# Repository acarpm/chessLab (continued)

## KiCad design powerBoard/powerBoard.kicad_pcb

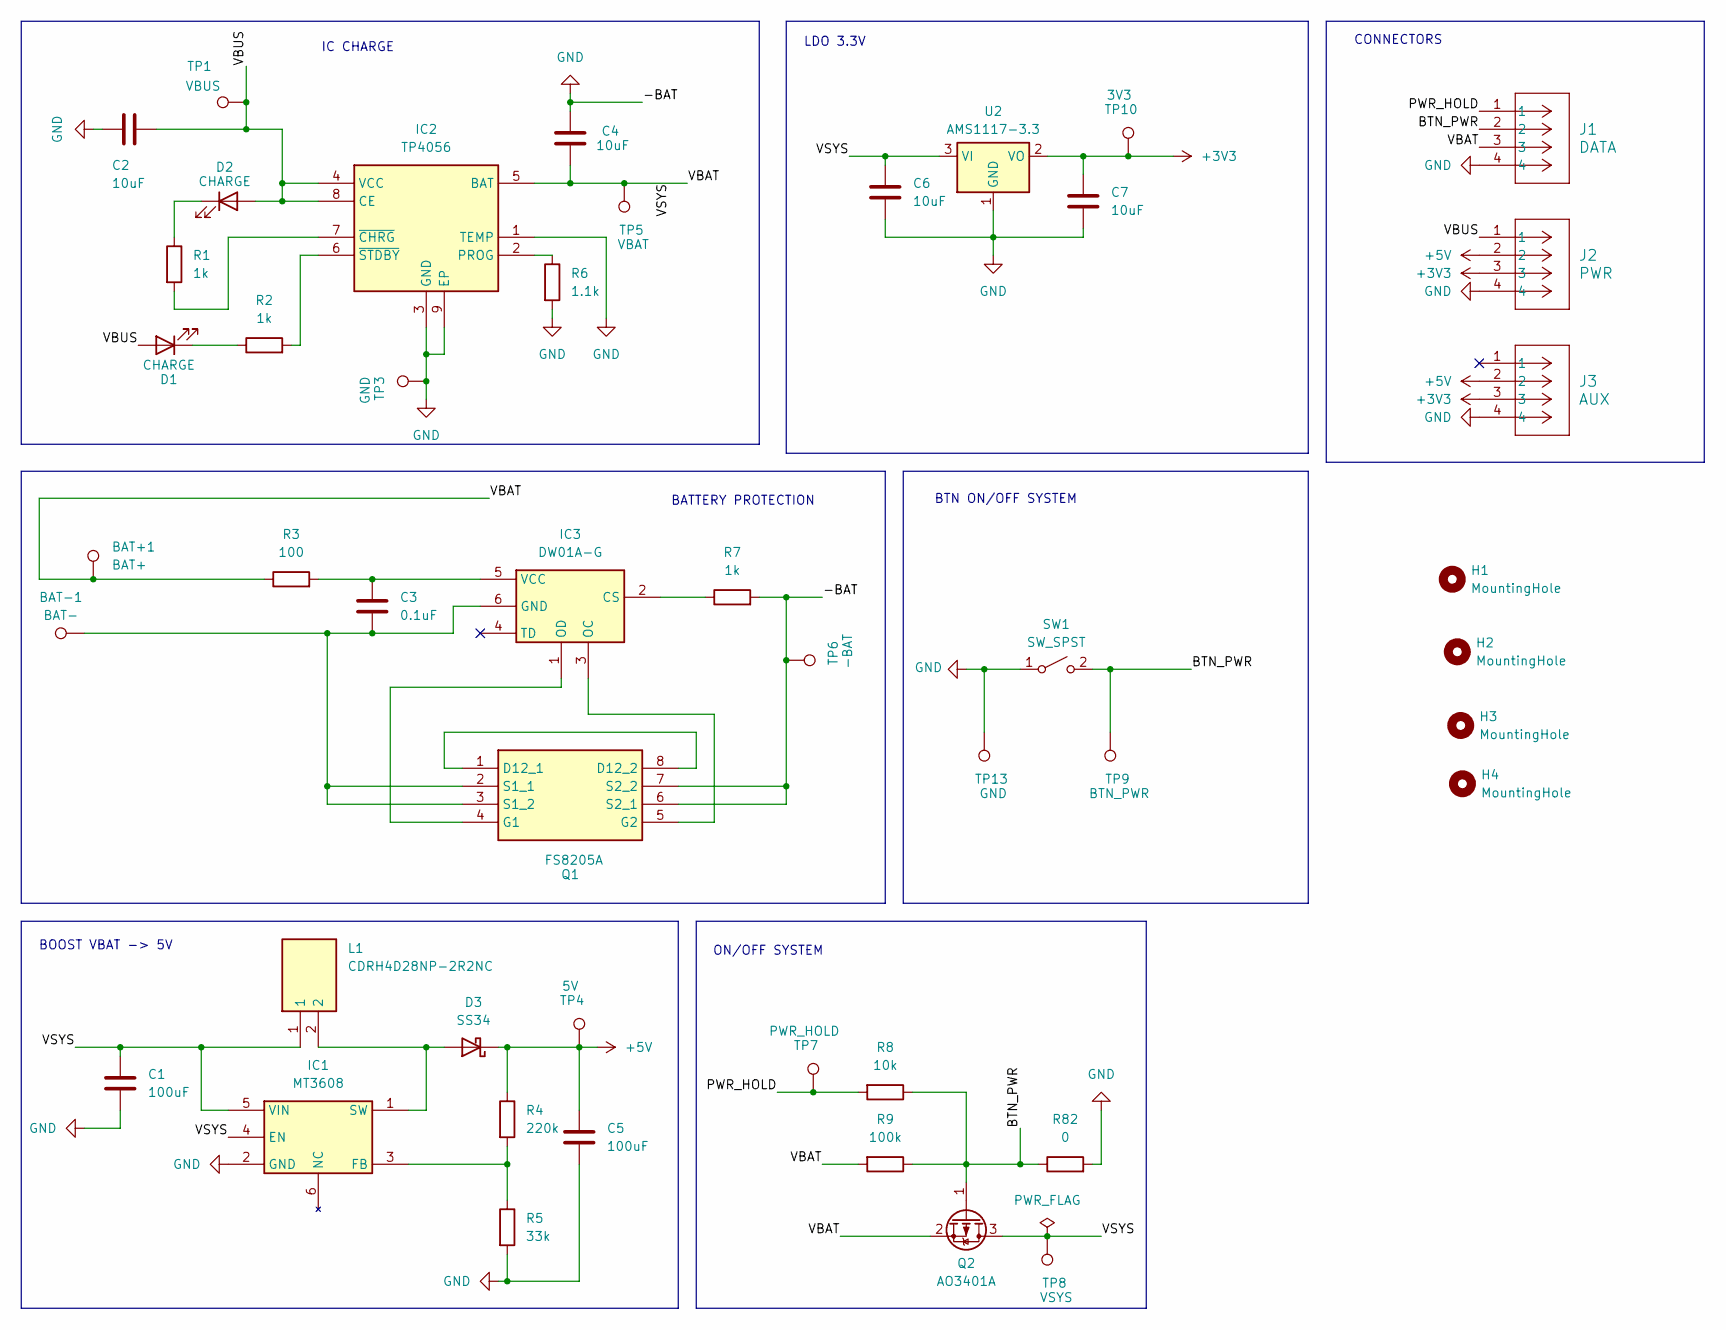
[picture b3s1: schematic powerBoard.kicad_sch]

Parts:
BAT+1: BAT+; TestPoint_Pad_4.0x4.0mm
BAT-1: BAT-; TestPoint_Pad_4.0x4.0mm
C1, C5: 100uF; C_1206_3216Metric_Pad1.33x1.80mm_HandSolder
C2, C4, C6, C7: 10uF; C_0603_1608Metric_Pad1.08x0.95mm_HandSolder
C3: 0.1uF; C_0603_1608Metric_Pad1.08x0.95mm_HandSolder
D1, D2: CHARGE; LED_0603_1608Metric_Pad1.05x0.95mm_HandSolder
D3: SS34; D_SMA
H1, H2, H3, H4: MountingHole; MountingHole_2.7mm_M2.5
IC1: MT3608; SOT95P280X145-6N; Manufacturer_Part_Number MT3608
IC2: TP4056; SOIC127P600X175-9N; Manufacturer_Part_Number TP4056
IC3: DW01A-G; SOT95P280X135-6N; Manufacturer_Part_Number DW01A-G
J1: DATA; JST_XH_B4B-XH-A_1x04_P2.50mm_Vertical
J2: PWR; JST_XH_B4B-XH-A_1x04_P2.50mm_Vertical
J3: AUX; JST_XH_B4B-XH-A_1x04_P2.50mm_Vertical
L1: CDRH4D28NP-2R2NC; CDRH4D28NP100NC; Mouser Part Number 851-CDRH4D28NP-2R2NC
Q1: FS8205A; SOP65P640X120-8N; Manufacturer_Part_Number FS8205A
Q2: AO3401A; SOT-23_Handsoldering
R1, R2, R7: 1k; R_0603_1608Metric_Pad0.98x0.95mm_HandSolder
R3: 100; R_0603_1608Metric_Pad0.98x0.95mm_HandSolder
R4: 220k; R_0603_1608Metric_Pad0.98x0.95mm_HandSolder
R5: 33k; R_0603_1608Metric_Pad0.98x0.95mm_HandSolder
R6: 1.1k; R_0603_1608Metric_Pad0.98x0.95mm_HandSolder
R8: 10k; R_0603_1608Metric_Pad0.98x0.95mm_HandSolder
R9: 100k; R_0603_1608Metric_Pad0.98x0.95mm_HandSolder
R82: 0; R_0603_1608Metric_Pad0.98x0.95mm_HandSolder
SW1: SW_SPST; B3U-1000P
TP1: VBUS; TestPoint_Pad_D2.0mm
TP3, TP13: GND; TestPoint_Pad_D2.0mm
TP4: 5V; TestPoint_Pad_D2.0mm
TP5: VBAT; TestPoint_Pad_D2.0mm
TP6: -BAT; TestPoint_Pad_D2.0mm
TP7: PWR_HOLD; TestPoint_Pad_D2.0mm
TP8: VSYS; TestPoint_Pad_D2.0mm
TP9: BTN_PWR; TestPoint_Pad_D2.0mm
TP10: 3V3; TestPoint_Pad_D2.0mm
U2: AMS1117-3.3; SOT-223-3_TabPin2

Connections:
+3V3: C7.1, J2.3, J3.3, TP10.1, U2.2 (VO)
+5V: C5.1, D3.1 (K), J2.2, J3.2, R4.1, TP4.1
/BTN_PWR: J1.2, Q2.1 (G), R8.1, R9.1, R82.1, SW1.2 (B), TP9.1; also elsewhere on the board
/PWR_HOLD: J1.1, R8.2, TP7.1
/VBAT: BAT+1.1, C1.1, C4.1, C6.1, IC1.4 (EN), IC1.5 (VIN), IC2.5 (BAT), J1.3, L1.1, Q2.2 (S), Q2.3 (D), R3.1, R9.2, TP5.1, TP8.1, U2.3 (VI)
/VBUS: C2.2, D1.2 (A), D2.2 (A), IC2.4 (VCC), IC2.8 (CE), J2.1, TP1.1
GND: C1.2, C2.1, C4.2, C5.2, C6.2, C7.2, IC1.2 (GND), IC2.1 (TEMP), IC2.3 (GND), IC2.9 (EP), J1.4, J2.4, J3.4, Q1.6 (S2_1), Q1.7 (S2_2), R5.2, R6.2, R7.2, R82.2, SW1.1 (A), TP3.1, TP6.1, TP13.1, U2.1 (GND); also elsewhere on the board
unnamed: D1.1 (K), R2.1
unnamed: D2.1 (K), R1.1
unnamed: D3.2 (A), IC1.1 (SW), L1.2
unnamed: IC1.3 (FB), R4.2, R5.1
unnamed: IC2.2 (PROG), R6.1
unnamed: IC2.7 (~CHRG), R1.2
unnamed: IC2.6 (~STDBY), R2.2
unnamed: IC3.2 (CS), R7.1
unnamed: BAT-1.1, C3.2, IC3.6 (GND), Q1.2 (S1_1), Q1.3 (S1_2)
unnamed: IC3.3 (OC), Q1.5 (G2)
unnamed: IC3.1 (OD), Q1.4 (G1)
unnamed: C3.1, IC3.5 (VCC), R3.2
unnamed: Q1.1 (D12_1), Q1.8 (D12_2)

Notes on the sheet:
BTN ON/OFF SYSTEM
BOOST VBAT -> 5V
CONNECTORS
ON/OFF SYSTEM
BATTERY PROTECTION
LDO 3.3V
IC CHARGE

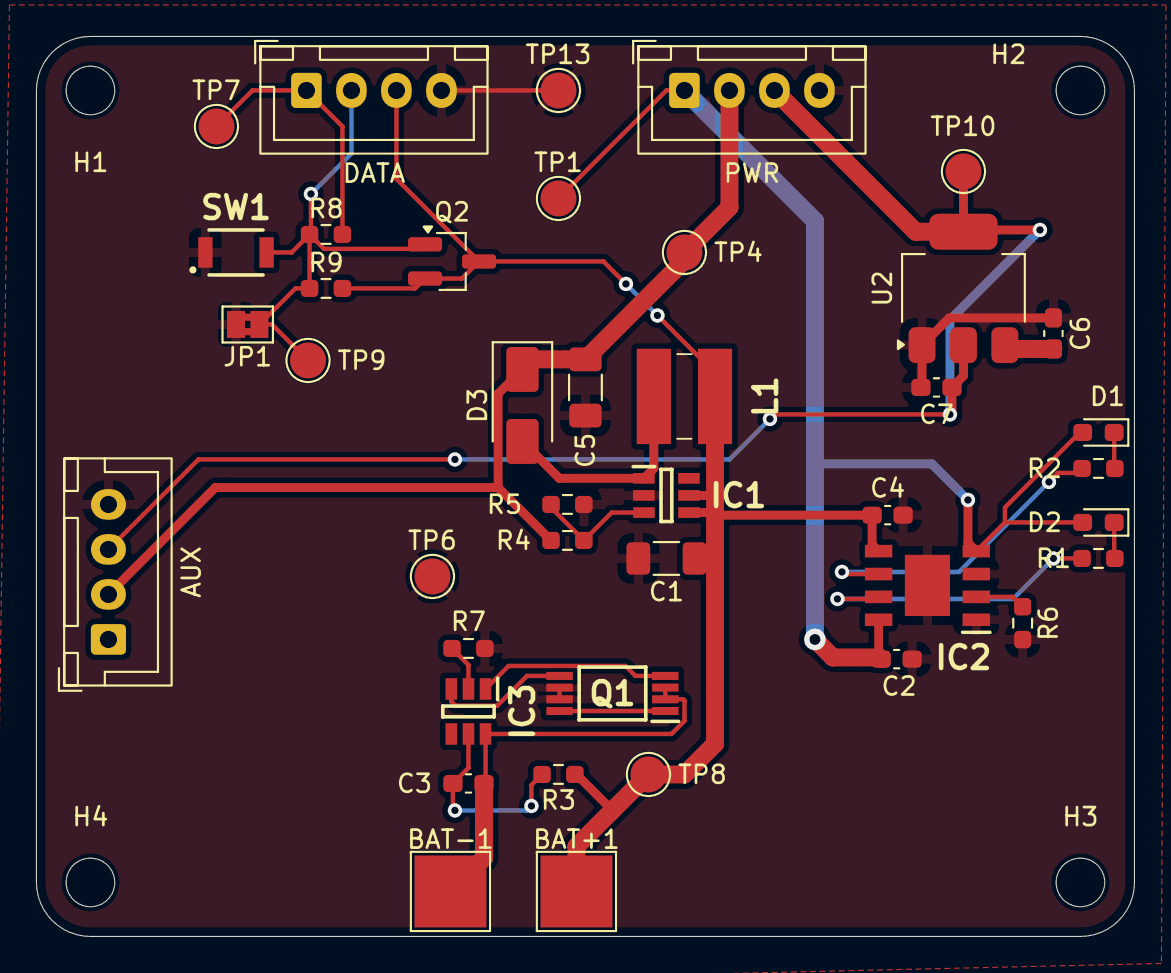
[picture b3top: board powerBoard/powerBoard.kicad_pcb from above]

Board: 2 copper layers, 61.0 x 50.0 mm, 45 parts (0 on the bottom side), 20 nets.

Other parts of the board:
JP1: SolderJumper_2_Bridged; SolderJumper-2_P1.3mm_Bridged2Bar_Pad1.0x1.5mm

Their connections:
/BTN_PWR: JP1.1 (A); also elsewhere on the board
GND: JP1.2 (B); also elsewhere on the board

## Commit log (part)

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2026-03-03 Inclusion of KiCad Project
2026-03-03 Include Lib and readme changes
2026-03-03 Readme Fix
2026-03-03 Kicad config
2026-03-04 KiCad Libs Config
2026-03-04 Svae
2026-03-04 Creation des Cellules et Fonctions de Multiplexage
    Organisation du projet KiCad en SousPages
    Creation des Fonctions Cell: Gestion individuelle de une case
    Row: Multiplexage de 8 cell
    Main Board:
    Liaisons avec ESP32C6
2026-03-04 KiCad Bug Fix
2026-03-05 Main Board update
2026-03-06 Finished Schematics
2026-03-06 Complete Schematics
2026-03-06 Update GitIgnore
2026-03-06 Fixing some footprints that were missmatched and issues with components import to pcb
2026-03-07 PCB SetUp
2026-03-07 Hall effect Replaced and 3d files uploaded
2026-03-08 Pcb Continued
2026-03-09 Update PCB
2026-03-17 Placement
2026-03-17 asaa
2026-03-27 maj pcb
2026-03-28 Clean Up Power Board
2026-03-28 Via stitch
2026-03-28 Final PCB chess
2026-03-29 power pcb
2026-04-01 PowerBoard pcb FRev2
2026-04-01 Power Board FREV2
2026-05-05 Rearrange + Code init
2026-05-05 Half way
2026-05-06 save
2026-05-07 manual test
2026-05-07 hall test
2026-05-12 Rows OK
2026-05-13 Hall Works
2026-05-13 Hall Fix
2026-05-13 Refactor ChessLab firmware into modular structure for improved maintainability and scalability
2026-05-13 FIX telnet and OPA
2026-05-13 WEB Interface
2026-05-14 Initial Game conditions verif
2026-06-04 refactor: relier le bouton poussoir à l'esp32
2026-06-04 Diodes size fix
2026-06-04 hist
2026-06-05 ajout des vias et le nom sur la carte
2026-06-06 Enhance README formatting
2026-06-08 AJOUT DES NOMS SUR LES CONNECTEURS EXTERIEURS
2026-06-08 Ajout des via et les noms sur la carte
2026-06-08 ajout de via et les noms sur la carte
2026-06-19 feat: add neopixel leds driver
2026-06-19 refactor: rename .h to .hpp
2026-06-19 fix: serial logging on linux
2026-06-19 refactor: architecture, add hall hal and driver
2026-06-19 fix: change board[row][col] to board[col][row]
    Example :
    Serial.println("Case A1 value: " + String(board[0][0]));
    Serial.println("Case B5 value: " + String(board[1][4]));
    Serial.println("Case C3 value: " + String(board[2][2]));
    Serial.println();
2026-06-19 refactor(HallMatrix): replace square[8][8] to a bitboard
